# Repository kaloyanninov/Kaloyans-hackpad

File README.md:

# Kaloyans Hackpad

---

## Bill of Materials (BOM)

### Parts I will need from the care package

* MX‑style mechanical switches (**8x**) 
* Blank DSA keycaps – **White** (**8x**)
* Rotary encoder EC11E 
* XIAO RP2040-dip
* SK6812 MINI‑E (**3x**)
* M3 × 16 mm screws (**4x**)
* M3 heat‑set inserts (**4x**)

---

### PCB

* The PCB i made has all of the parts that I have listed above. I tried to make the PCB traces organized.
* 
* This is the schematic.
* 
* This is the full assembly.
* 

---

## Assembly 

* The PCB will just be put in the bottom case withoout securing it.
* The top plate will make the PCB and switches stay in one place without wobling much
* After that the top plate issecured to the bottom case with the provided bolts

---

## Firmware

* This project will use KMK firmware/code. The code before i get the hackpad will be form AI, but ill improve 
  
---

Perfect for:

* Coding shortcuts
* Learning how to write keyboard firmware

---

## Credits

* Designed and built by *(kaloyanninov)*
* Inspired by open‑source mechanical keyboard and hackpad communities (https://blueprint.hackclub.com/home).

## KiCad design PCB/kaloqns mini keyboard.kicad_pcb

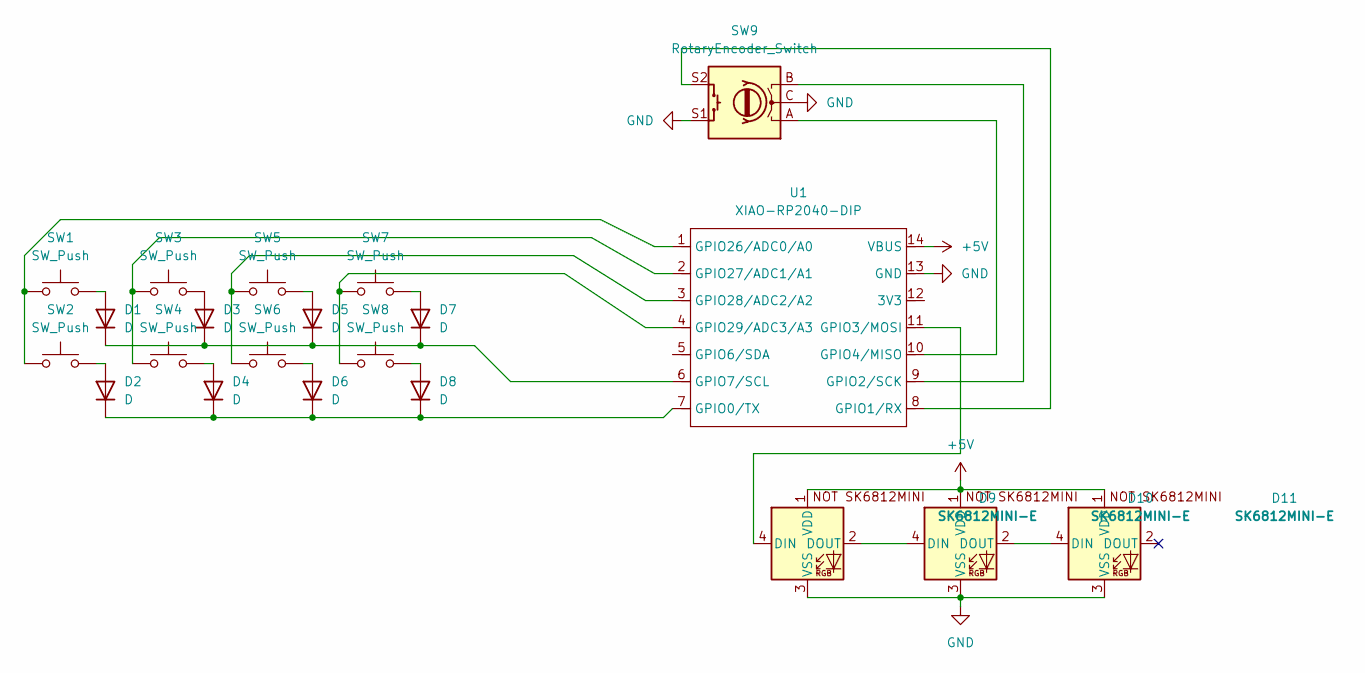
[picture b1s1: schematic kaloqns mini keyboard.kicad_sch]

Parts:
D1, D2, D3, D4, D5, D6, D7, D8: D; D_DO-35_SOD27_P7.62mm_Horizontal
D9, D10, D11: SK6812MINI-E; SK6812MINI-E_fixed
SW1, SW2, SW3, SW4, SW5, SW6, SW7, SW8: SW_Push; SW_Cherry_MX_1.00u_PCB
SW9: RotaryEncoder_Switch; RotaryEncoder_Alps_EC11E-Switch_Vertical_H20mm
U1: XIAO-RP2040-DIP

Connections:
+5V: D9.1 (VDD), D10.1 (VDD), D11.1 (VDD), U1.14 (VBUS)
GND: D9.3 (VSS), D10.3 (VSS), D11.3 (VSS), SW9.C, SW9.S1, U1.13 (GND)
unnamed: D1.2 (A), SW1.2
unnamed: D1.1 (K), D3.1 (K), D5.1 (K), D7.1 (K), U1.6 (GPIO7/SCL)
unnamed: D2.2 (A), SW2.2
unnamed: D2.1 (K), D4.1 (K), D6.1 (K), D8.1 (K), U1.7 (GPIO0/TX)
unnamed: D3.2 (A), SW3.2
unnamed: D4.2 (A), SW4.2
unnamed: D5.2 (A), SW5.2
unnamed: D6.2 (A), SW6.2
unnamed: D7.2 (A), SW7.2
unnamed: D8.2 (A), SW8.2
unnamed: D9.4 (DIN), U1.11 (GPIO3/MOSI)
unnamed: D9.2 (DOUT), D10.4 (DIN)
unnamed: D10.2 (DOUT), D11.4 (DIN)
unnamed: SW9.S2, U1.8 (GPIO1/RX)
unnamed: SW9.B, U1.9 (GPIO2/SCK)
unnamed: SW9.A, U1.10 (GPIO4/MISO)
unnamed: SW1.1, SW2.1, U1.1 (GPIO26/ADC0/A0)
unnamed: SW3.1, SW4.1, U1.2 (GPIO27/ADC1/A1)
unnamed: SW5.1, SW6.1, U1.3 (GPIO28/ADC2/A2)
unnamed: SW7.1, SW8.1, U1.4 (GPIO29/ADC3/A3)

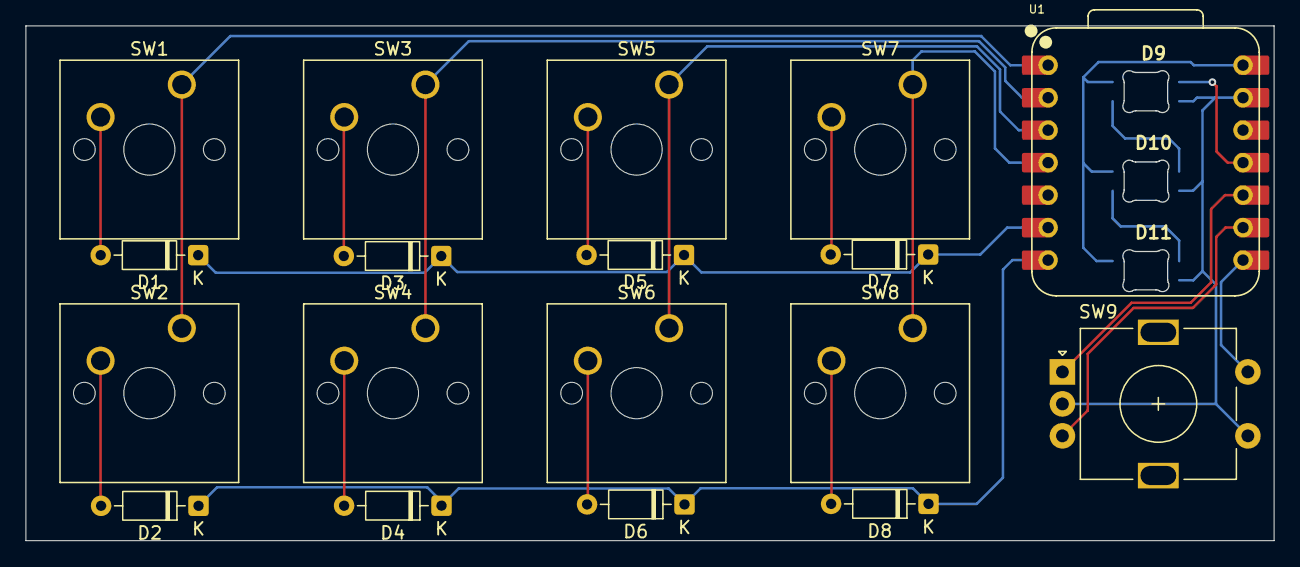
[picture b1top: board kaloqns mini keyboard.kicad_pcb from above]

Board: 2 copper layers, 97.6 x 40.2 mm, 21 parts (0 on the bottom side), 22 nets.

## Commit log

2026-03-01 File update
